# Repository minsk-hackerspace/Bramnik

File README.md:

# Bramnik

Bramnik (gatekeeper in Belarussian) is an Open Source DIY smart lock for entrance authorization.

It synchronizes own user DB with your CMS or whatever application you use for user keeping.

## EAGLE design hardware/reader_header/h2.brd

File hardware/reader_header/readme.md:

Reader header:
---------

Just header board for Ras perry Pi features:

- DC/DC converter supply power for Rasperry Pi
- converts i2c from 3.3v Rasperry Pi to 5v Arduino
- Arduino with onboard logic and additional Mosfet 
- Connectors for connecting any external NFC/reader/keypad (weigant)

Raspi Header Scheme:
-------

Protocol:
---------

TODO:

TODO:
-----

add readme

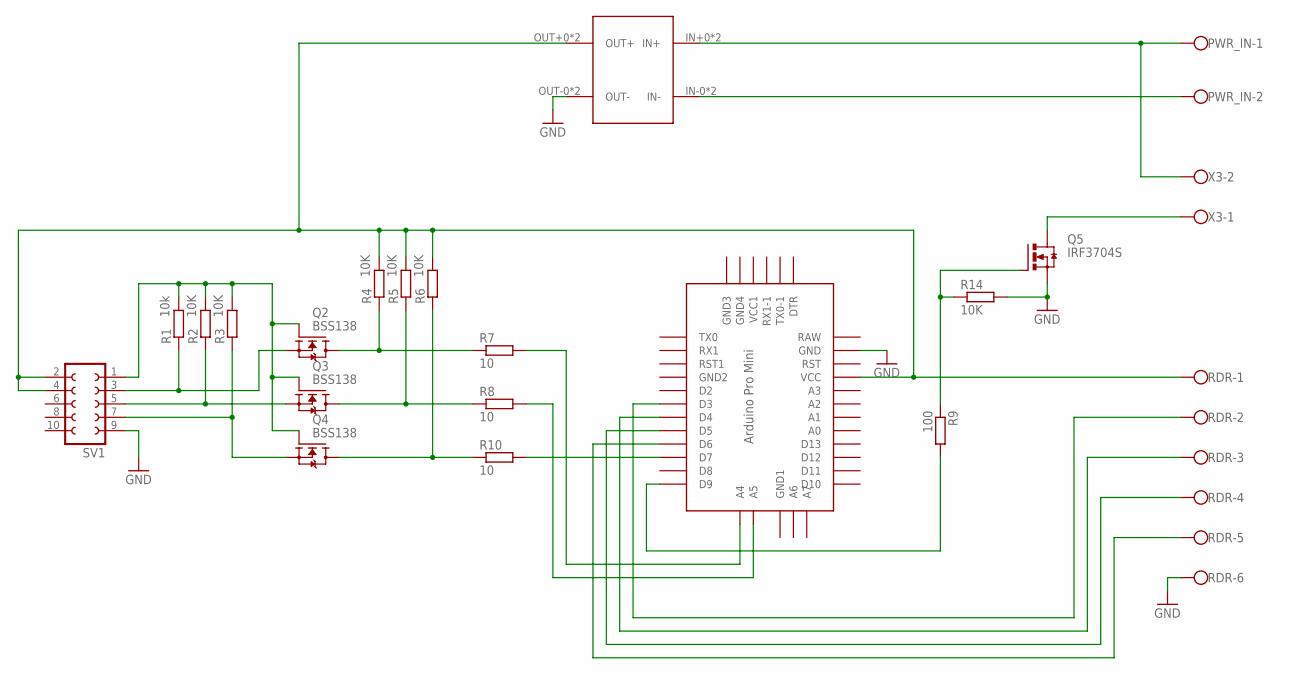
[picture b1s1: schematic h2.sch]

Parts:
PWR_IN: W237-102
Q2, Q3, Q4: BSS138; SOT23
Q5: IRF3704S; D2PACK
R1: 10k; R1206
R2, R3, R4, R5, R6, R14: 10K; R1206
R7, R8, R10: 10; R1206
R9: 100; R1206
RDR: W237-136
SV1: FE05-2
U$1: DC/DC4.5-20-ADJ; 23X17_8P
U$4: ABK-PRO-MINI
X3: W237-102

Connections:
GND: Q5.3 (S), R14.2, RDR.6, SV1.9, U$1.OUT-0 (OUT-), U$1.OUT-1 (OUT-), U$4.GND
unnamed: Q2.2 (S), R1.1, SV1.3
unnamed: Q2.1 (G), Q3.1 (G), Q4.1 (G), R1.2, R2.2, R3.2, SV1.1
unnamed: Q2.3 (D), R4.1, R7.1
unnamed: Q3.2 (S), R2.1, SV1.5
unnamed: Q4.2 (S), R3.1, SV1.7
unnamed: R8.2, U$4.A5
unnamed: RDR.2, U$4.D3
unnamed: R4.2, R5.2, R6.2, RDR.1, SV1.2, SV1.4, U$1.OUT+0 (OUT+), U$1.OUT+1 (OUT+), U$4.VCC
unnamed: R10.2, U$4.D7
unnamed: Q3.3 (D), R5.1, R8.1
unnamed: Q4.3 (D), R6.1, R10.1
unnamed: R7.2, U$4.A4
unnamed: PWR_IN.2, U$1.IN-0 (IN-), U$1.IN-1 (IN-)
unnamed: Q5.2 (D), X3.1
unnamed: R9.2, U$4.D9
unnamed: Q5.1 (G), R9.1, R14.1
unnamed: RDR.3, U$4.D4
unnamed: RDR.4, U$4.D5
unnamed: RDR.5, U$4.D6
PWR+12: PWR_IN.1, U$1.IN+0 (IN+), U$1.IN+1 (IN+), X3.2

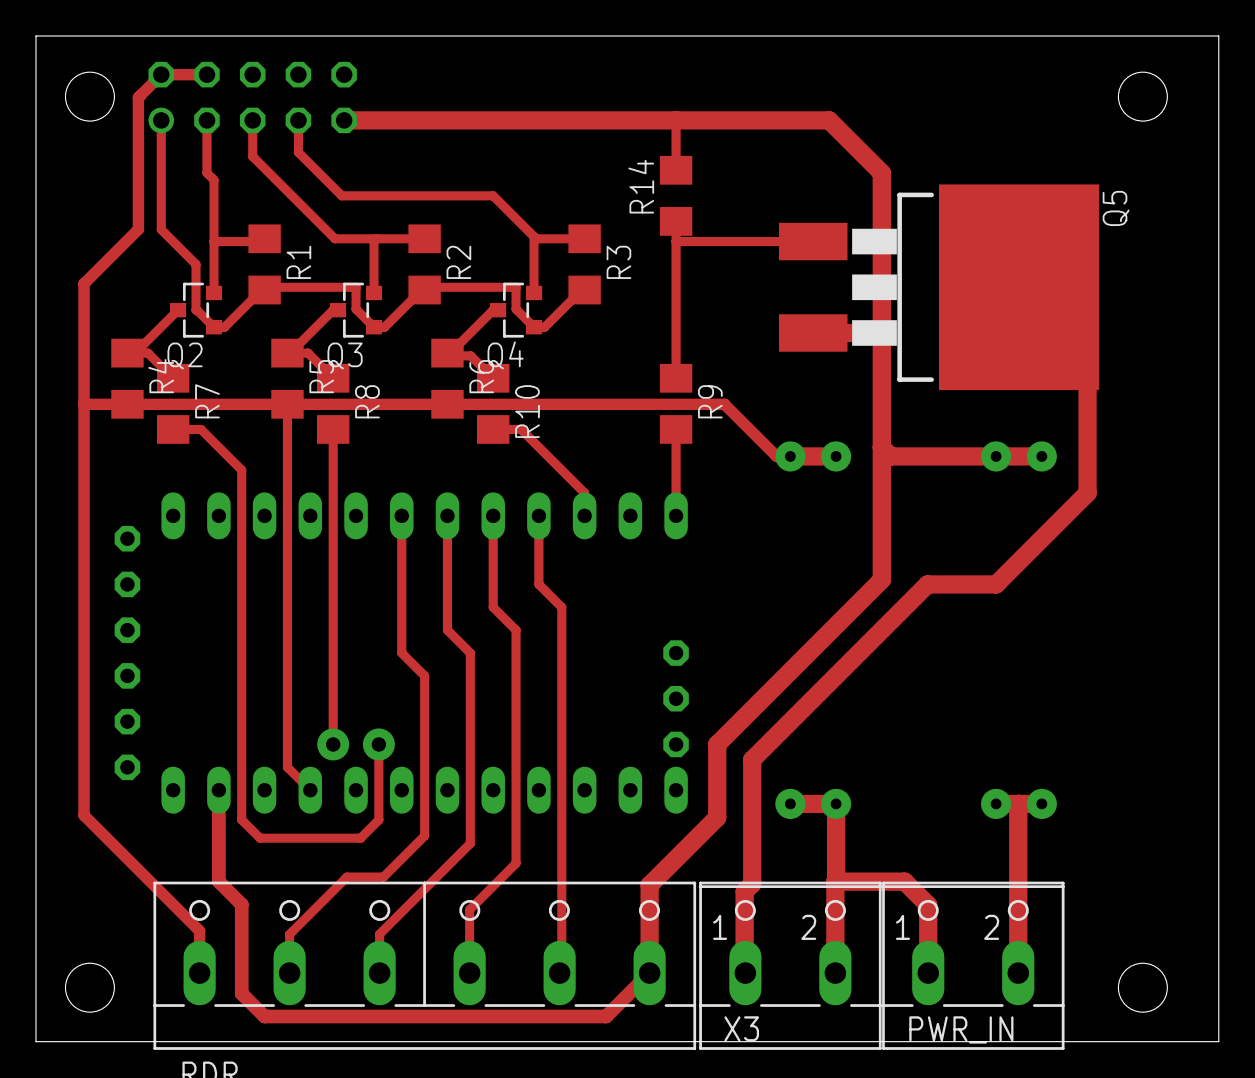
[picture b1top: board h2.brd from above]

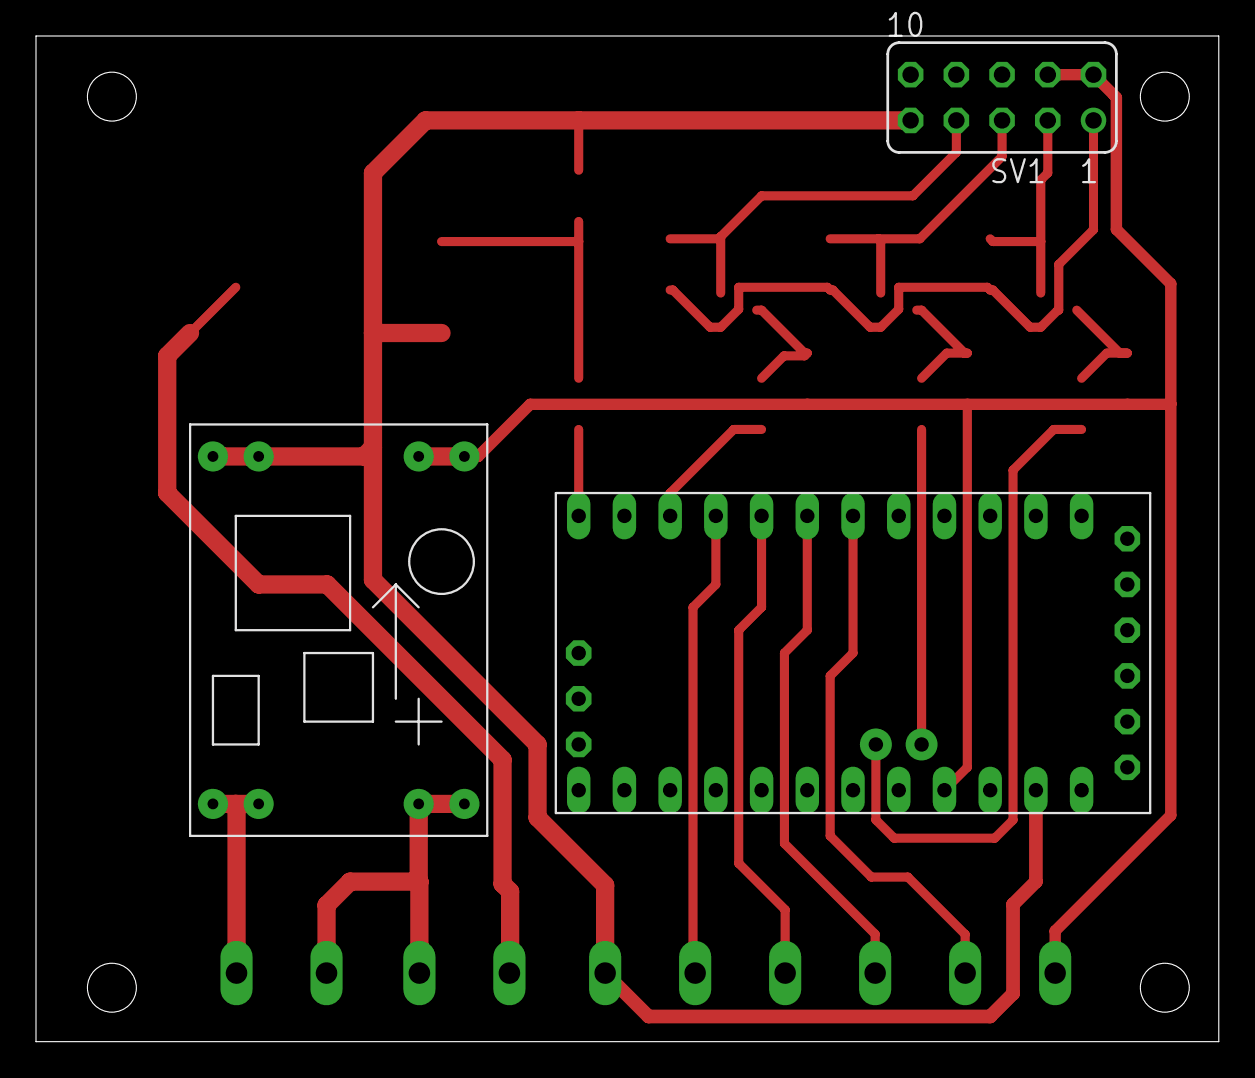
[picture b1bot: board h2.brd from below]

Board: 2 copper layers, 65.7 x 55.9 mm, 21 parts (3 on the bottom side), 21 nets.

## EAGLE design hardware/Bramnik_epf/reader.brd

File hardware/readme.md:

Interface:
---------

Host Raspbbery Pi (i2c master) <->  (i2c slave) Reader Header Arduino <-> Weigant reader

Protocol:
---------

TODO:

Reader Header:
-------

https://github.com/minsk-hackerspace/Bramnik/tree/master/hardware/reader_header

TODO:
-----

add readme

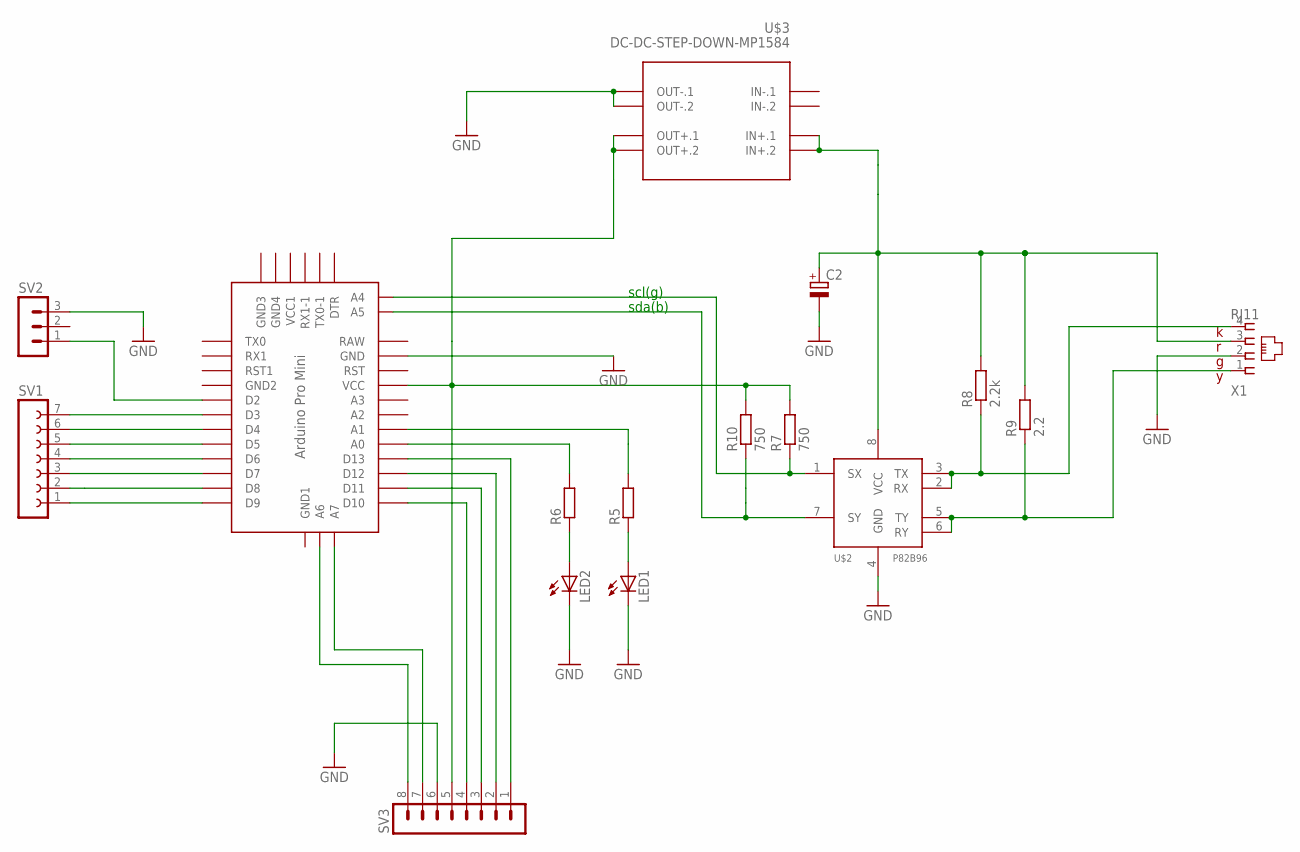
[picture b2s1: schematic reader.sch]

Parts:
C2: CPOL-EUE5-6; E5-6
LED1, LED2: LEDB152; Q62902-B152
R5, R6: R-EU_M1206; M1206
R7, R10: 750; M1206
R8: 2.2k; M1206
R9: 2.2; M1206
SV1: FE07-1; FE07
SV2: MA03-1
SV3: MA08-1
U$1: ABK-PRO-MINI
U$2: P82B96_; SOIC8
U$3: DC-DC-STEP-DOWN-MP1584
X1: RJ11; RJ11-4P4C

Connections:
GND: C2.-, LED1.K (C), LED2.K (C), SV2.3, SV3.6, U$1.GND, U$2.4 (GND), U$3.OUT-.1, U$3.OUT-.2, X1.2
unnamed: SV1.1, U$1.D9
unnamed: R7.1, U$1.A4, U$2.1 (SX)
unnamed: R10.1, U$1.A5, U$2.7 (SY)
unnamed: R8.1, U$2.2 (RX), U$2.3 (TX), X1.4
unnamed: SV3.1, U$1.D13
unnamed: R9.1, U$2.5 (TY), U$2.6 (RY), X1.1
unnamed: SV1.2, U$1.D8
unnamed: C2.+, R8.2, R9.2, U$2.8 (VCC), U$3.IN+.1, U$3.IN+.2, X1.3
unnamed: SV1.3, U$1.D7
unnamed: SV1.4, U$1.D6
unnamed: SV1.5, U$1.D5
unnamed: SV1.6, U$1.D4
unnamed: SV1.7, U$1.D3
unnamed: SV3.2, U$1.D12
unnamed: SV2.1, U$1.D2
unnamed: R5.2, U$1.A1
unnamed: R6.2, U$1.A0
unnamed: LED1.A, R5.1
unnamed: LED2.A, R6.1
unnamed: SV3.3, U$1.D11
unnamed: R7.2, R10.2, SV3.5, U$1.VCC, U$3.OUT+.1, U$3.OUT+.2
unnamed: SV3.4, U$1.D10
unnamed: SV3.7, U$1.A7
unnamed: SV3.8, U$1.A6

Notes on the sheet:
scl(g)
sda(b)

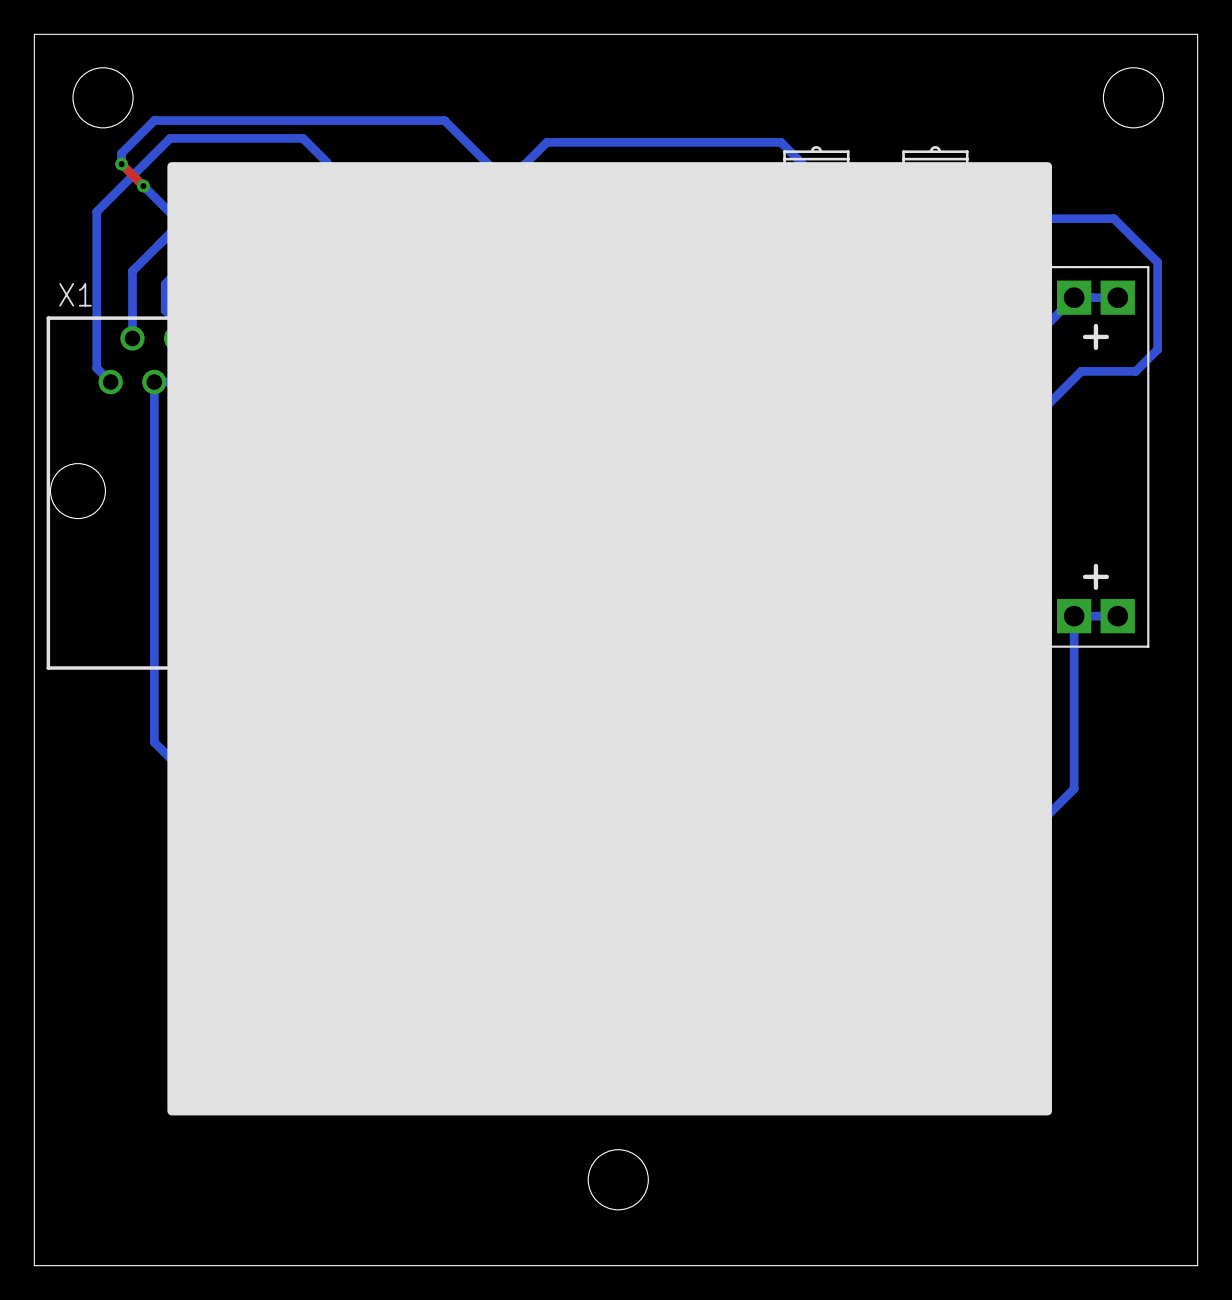
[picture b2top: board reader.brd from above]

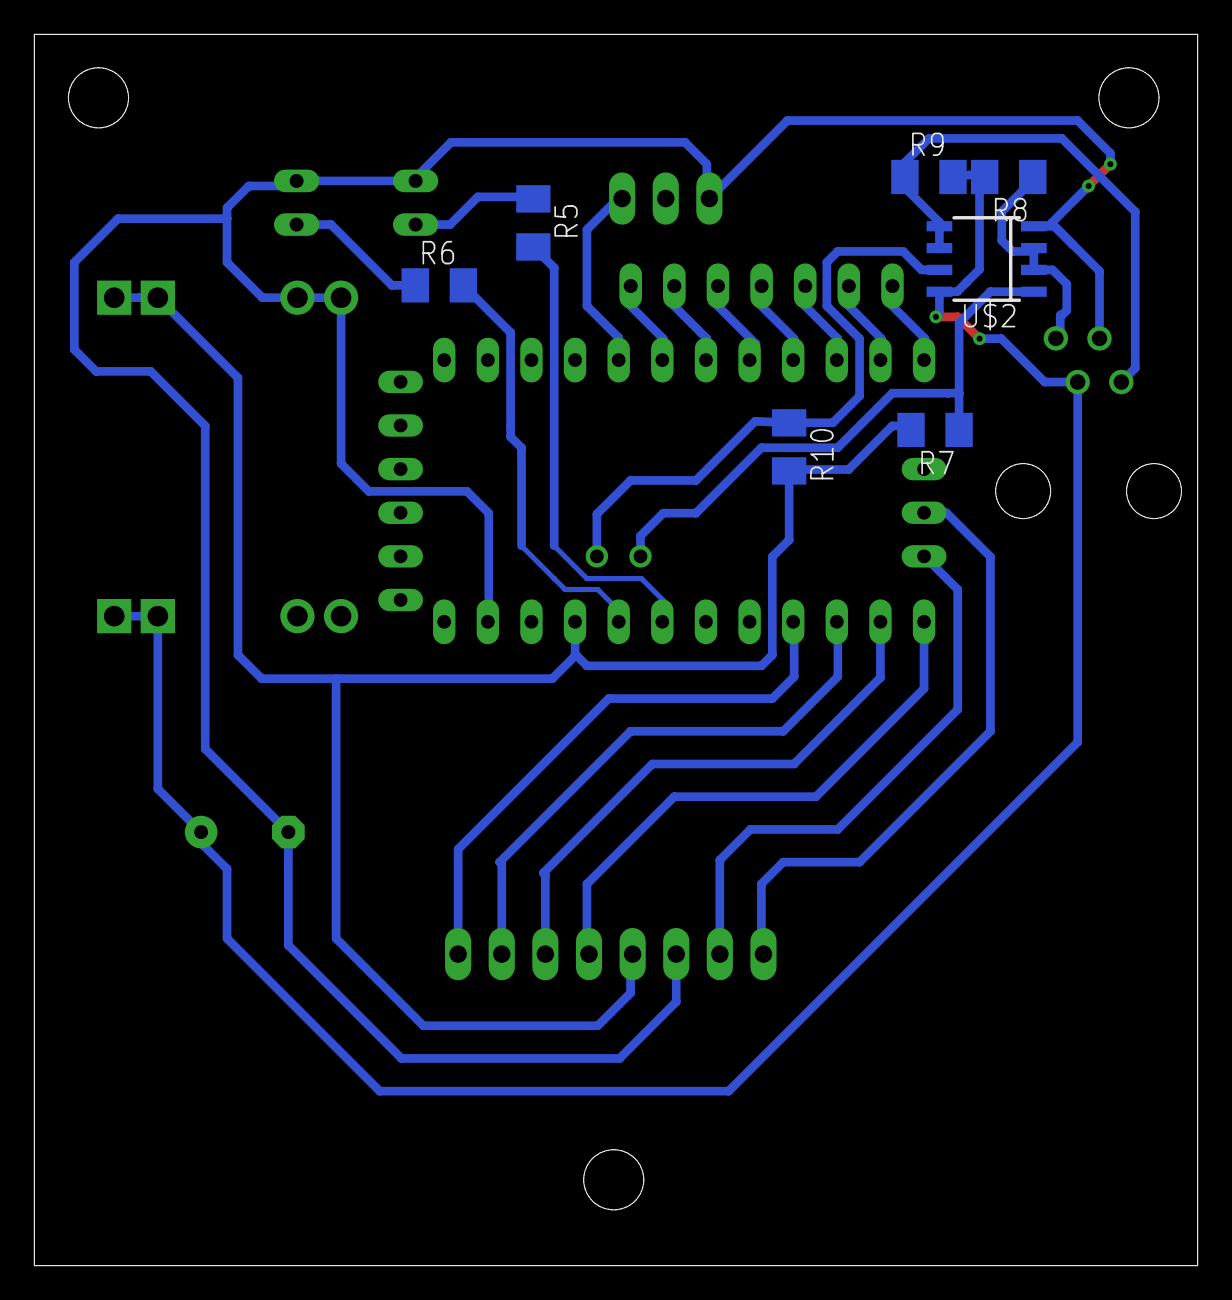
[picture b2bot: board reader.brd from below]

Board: 2 copper layers, 67.7 x 71.7 mm, 16 parts (7 on the bottom side), 25 nets.

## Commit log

2016-09-07 Add reader external connector specification
2016-09-07 Add image of the printed version
2017-04-03 Add first scheme Update i2c long distance
2017-04-03 Add test i2c scetch
2017-04-03 Update readme.md
    add image
2017-04-04 Update readme.md
    Add sample protocol communication between reader and host
2017-04-28 add photos to readme
2017-04-30 add host case
2017-05-21 Some bram code update
2017-05-21 - NFC report debounce. Added wire NFC reporting code as comment
2017-05-22 - Blindly merge wire code. Tests on hardware are needed.
2017-05-22 Update readme.md
    Fix pins names
2017-05-22 Update NFC reader code
2017-05-24 - Define to suppress logging
2017-05-24 add host scripts
2017-05-24 Revert "add host scripts"
    This reverts commit cc6db39bba0f3380c05286e597d6ac3cf59e895f.
2017-05-24 add host files'
2017-05-24 Add enable/disable functions
2017-05-24 add some keys funcs
2017-05-25 - Implement Keypad data reading
2017-05-25 host works
2017-05-25 tune some music for feedback
2017-05-25 Fix some pithes
2017-05-26 god added
2017-05-26 absolute paths to files
2017-06-19 Update melody playing code
2018-09-02 ruby update
2018-09-03 Upd ardu scetch
2018-09-03 Upd scheme
2018-09-03 Upd scheme image
2019-01-19 Update reader code
2019-01-19 Fix timings
2019-01-20 Add open door sensor
2019-01-20 Update reset cycles
2019-01-21 python version of host software
2019-01-21 log format change
2019-01-21 control log level from command line
2019-01-21 systemd related stuff
2019-01-21 wsBcBAABCAAQBQJcRh04CRBK7hj4Ov3rIwAAdHIIADFOBuA9k5lcBtMdz5UH+Dsj +fwmI2oEjNEv2MblM1/cDa9/yJBGTfsYYmDf2aIkHWS068CZuV5lAdiyQkEgcw6C DlGZ5YDoMYTQbdVhTcooe6D2t6hlVYBnZtQJZN1GKr/n2cXlRqCHMQVVCKDnMPth Nkiw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
    Update Readme.md
    syntax changes
2019-01-21 wsBcBAABCAAQBQJcRh1eCRBK7hj4Ov3rIwAAdHIIADHe74GtcoTLahPfDi3CuYwg RVfK2zx6abeC7QyjO3NXx7yxxjLMkb2OaPNl61c8pY8iy/vDF2/z0L3EHymgyn/c cKv8PiJt5fGJxoMEf2fhWivBGSbmtAjNh8+7vjbCOWw0daKDIQ/XWo2vOaJt42Wf Gk1Y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
    Update Readme.md
2019-01-21 wsBcBAABCAAQBQJcRj4qCRBK7hj4Ov3rIwAAdHIIAJiWUrZPRphFT9DJHLmFmAhD qjx20qWZx2rLT4/Lw6f5ZSRwHA1xCPUpPTu+v+WdMh2FDNb1MSG1EAtqDAcRF4y0 qliQObwGzjwuUtIz/dA7v7wqiINsW/QtSG/srDCqiK6//O1iP4tzr8BH6YGW7LFC Vlrq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
    Update Readme.md
    python doc enhancements
2019-01-21 wsBcBAABCAAQBQJcRj6PCRBK7hj4Ov3rIwAAdHIIAFhmX+cb/ary3T+6VXlLHqzC /VR/zeQApMfPdF9WJnYRELQMlxMjPIKC1TucBhJml1U2r+c1HJUcLdBmOCY951VC IAhjLBHIg7Hcw1LZxFCxUXIT3KTY8MwX+SemWT5nH5YIfuaIW9Kedcc01we8WKHc 7FIl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
    Delete hackers.json
2019-01-22 db scheme, CLI tool to work with db, NFC cards is being checked using db
2019-01-22 codes from db support
2019-01-23 list cards script
2019-01-23 list codes script, allow emitting codes for guests
2019-01-23 user sync from json
2019-12-28 Add examples for new reader HW (Wiegand reader plus arduino interface board)
2019-12-28 Bump ffi from 1.9.14 to 1.11.3 in /software/host
    Bumps [ffi](https://github.com/ffi/ffi) from 1.9.14 to 1.11.3.
    - [Release notes](https://github.com/ffi/ffi/releases)
    - [Changelog](https://github.com/ffi/ffi/blob/master/CHANGELOG.md)
    - [Commits](https://github.com/ffi/ffi/compare/1.9.14...1.11.3)
2020-01-18 Add reader v2 schematics
2020-02-29 Add READER HEADER
2020-03-01 Update reader soft
2020-03-01 Implement some commands
2020-03-01 Fix reader keys
2020-03-07 Code cleanup
2020-03-07 move some files
2020-03-07 readme update
2020-03-07 blind coding (rpi needed to run)
2020-03-07 fixes
2020-03-08 fix availability
2020-03-08 Fix card byte order
2020-03-08 Update sync, refactor logs, fix nfc code length
2020-03-08 Improve logging
2020-03-08 script for running sync
2020-03-08 cron sample
2021-03-02 Bump activerecord from 5.2.4.1 to 5.2.4.5 in /obsolete/software/host
    Bumps [activerecord](https://github.com/rails/rails) from 5.2.4.1 to 5.2.4.5.
    - [Release notes](https://github.com/rails/rails/releases)
    - [Changelog](https://github.com/rails/rails/blob/v6.1.3/activerecord/CHANGELOG.md)
    - [Commits](https://github.com/rails/rails/compare/v5.2.4.1...v5.2.4.5)
2021-03-07 host.py: Replace delay with thread synchronization events
2021-03-07 Set right pin for "open the lock" function
2021-03-07 Add button to open the door inside of hackerspace
2021-03-08 host: Add 14 days to paid_until field at calculating of access validity
2021-03-08 host: Remove NFC keys deleted in master db at sync
2021-03-08 host: Make temporary codes working
2021-03-11 Support for short codes (less than 8 digits)
2021-04-03 Add autoemitting of code for Open Days with telegram notifications
2021-04-03 Check the access_allowed field of user to deny access for remote hackers
2021-04-03 Remove binaries from git
2021-10-13 Up description
2021-10-17 host.py: Don't import SMBusWrapper (obsoleted)
2021-10-17 Remove all cards before adding them (#10)
2021-11-27 bramnik_mgr.py: Use python3 by default
2021-11-27 host.py: Add opening the door by USR1 signal
2021-11-27 host.py: Use constant to define IRQ pin number
2022-02-03 host.py: Add Telegram notifications about door opening
2022-02-05 bramnik_mgr: Save real user name to DB
2022-02-05 bramnik_mgr: Unindent old block
2022-02-05 Add user name to door opening Telegram notification
2022-02-05 host.py: Replace card.user by card.user_id
2022-02-05 bramnik_mgr: Fix emit code output (show user id instead of name)
2022-02-05 host.py: Don't expose code in Tg notifications
2022-02-10 host.py: Don't deny access at codes without of accociated user id
2022-03-25 Sync with installed version
2022-03-26 Remove obsoleted code
2022-03-26 Add README for reader firmware
2022-03-31 Fix invalid interpreter in emit_dod_code.sh
2022-12-24 Remove expired codes before creating new one

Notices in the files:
parts and their libraries:
diy-modules: Released under the Creative Commons Attribution 4.0 International License: http://creativecommons.org/licenses/by/4.0
